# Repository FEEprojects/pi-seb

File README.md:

# Pi-Seb

A PCB for the Raspberry Pi to create a flexible sensor evaluation board.

Provides the following features:
* HAT identification EEPROM
* 12V DC input
* Battery backed RTC
* Temperature/Humidity Sensor
* 8 differential ADC
* 23 GPIO
* 8 I2C connectors
* 4 SPI connectors
* Debug LEDs (can be disabled)
* 4 port USB hub
  * RS232 connection / TTL Serial
  * 2 TTL Serial ports
  * RS485 connection
* Pycom Socket
  * SD card
  * Control of Raspberry Pi Power
  * 2 TTL Serial ports
  * I2C connection
  * SPI port
  * 8 GPIO

## Assembly
Most of the passives and some of the semi conductors are available in the Seeed studio OPL, additional components then need to be sourced and hand soldred.

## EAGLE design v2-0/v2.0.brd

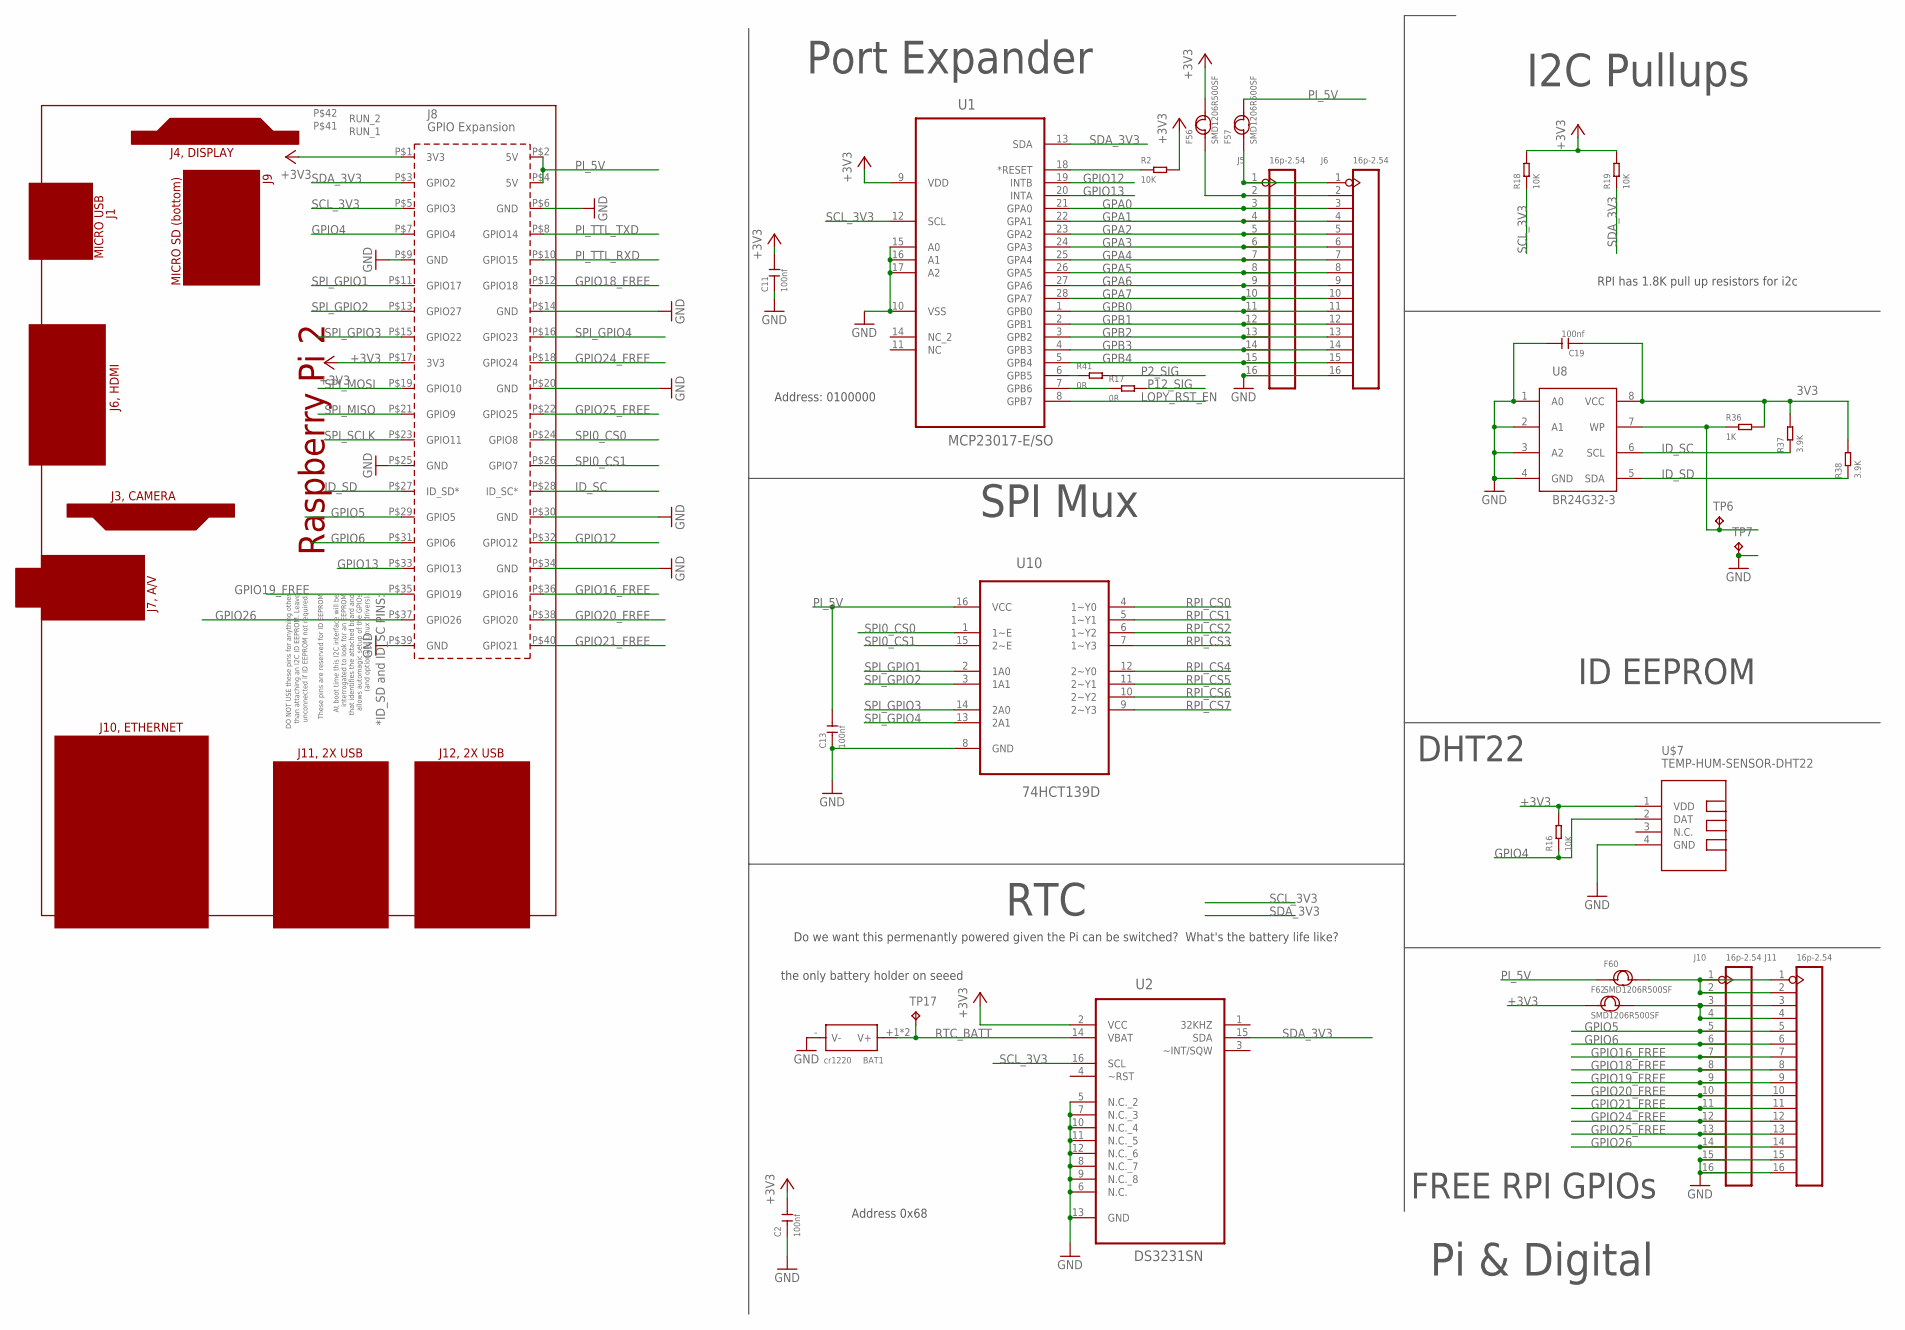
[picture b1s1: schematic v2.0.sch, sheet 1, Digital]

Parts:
BAT1: cr1220; BAT2P-13.5-CR1220
C2, C11, C13, C19: 100nf; C0603
F56, F57, F60, F62: SMD1206R500SF; F1206
J5, J6, J10, J11: 16p-2.54; H16-2.54
PCB1: RPI2
R2, R16, R18, R19: 10K; R0603
R17, R41: 0R; R0603
R36: 1K; R0603
R37, R38: 3.9K; R0603
TP6, TP7, TP17: TPB2,54; B2,54
U1: MCP23017-E/SO; SOIC127P1032X265-28N
U2: DS3231SN; SOIC127P1032X265-16N
U8: BR24G32-3; SOP8
U10: 74HCT139D; SOIC127P600X175-16N
U$7: TEMP-HUM-SENSOR-DHT22

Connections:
3V3: C19.1, R36.2, R37.2, R38.2, U8.8 (VCC)
+3V3: C2.2, C11.2, F56.2, F62.1, PCB1.P$1 (3V3), PCB1.P$17 (3V3), R2.2, R16.2, R18.2, R19.2, U1.9 (VDD), U2.2 (VCC), U$7.1 (VDD); also elsewhere on the board
EEPROM_WP: R36.1, TP6.TP, U8.7 (WP)
EXP_3V3: F56.1, J5.2, J6.2
EXP_5V: F57.1, J5.1, J6.1
GND: BAT1.- (V-), C2.1, C11.1, C13.1, C19.2, J5.16, J6.16, J10.15, J10.16, J11.15, J11.16, PCB1.P$6 (GND), PCB1.P$9 (GND), PCB1.P$14 (GND), PCB1.P$20 (GND), PCB1.P$25 (GND), PCB1.P$30 (GND), PCB1.P$34 (GND), PCB1.P$39 (GND), TP7.TP, U1.10 (VSS), U1.15 (A0), U1.16 (A1), U1.17 (A2), U2.5 (N.C._2), U2.6 (N.C.), U2.7 (N.C._3), U2.8 (N.C._7), U2.9 (N.C._8), U2.10 (N.C._4), U2.11 (N.C._5), U2.12 (N.C._6), U2.13 (GND), U8.1 (A0), U8.2 (A1), U8.3 (A2), U8.4 (GND), U10.8 (GND), U$7.4 (GND); also elsewhere on the board
GPA0: J5.3, J6.3, U1.21 (GPA0)
GPA1: J5.4, J6.4, U1.22 (GPA1)
GPA2: J5.5, J6.5, U1.23 (GPA2)
GPA3: J5.6, J6.6, U1.24 (GPA3)
GPA4: J5.7, J6.7, U1.25 (GPA4)
GPA5: J5.8, J6.8, U1.26 (GPA5)
GPA6: J5.9, J6.9, U1.27 (GPA6)
GPA7: J5.10, J6.10, U1.28 (GPA7)
GPB0: J5.11, J6.11, U1.1 (GPB0)
GPB1: J5.12, J6.12, U1.2 (GPB1)
GPB2: J5.13, J6.13, U1.3 (GPB2)
GPB3: J5.14, J6.14, U1.4 (GPB3)
GPB4: J5.15, J6.15, U1.5 (GPB4)
GPIO4: PCB1.P$7 (GPIO4), R16.1, U$7.2 (DAT)
GPIO5: J10.5, J11.5, PCB1.P$29 (GPIO5)
GPIO6: J10.6, J11.6, PCB1.P$31 (GPIO6)
GPIO12: PCB1.P$32 (GPIO12), U1.19 (INTB)
GPIO13: PCB1.P$33 (GPIO13), U1.20 (INTA)
GPIO16_FREE: J10.7, J11.7, PCB1.P$36 (GPIO16)
GPIO18_FREE: J10.8, J11.8, PCB1.P$12 (GPIO18)
GPIO19_FREE: J10.9, J11.9, PCB1.P$35 (GPIO19)
GPIO20_FREE: J10.10, J11.10, PCB1.P$38 (GPIO20)
GPIO21_FREE: J10.11, J11.11, PCB1.P$40 (GPIO21)
GPIO24_FREE: J10.12, J11.12, PCB1.P$18 (GPIO24)
GPIO25_FREE: J10.13, J11.13, PCB1.P$22 (GPIO25)
GPIO26: J10.14, J11.14, PCB1.P$37 (GPIO26)
GPIO_5V_FUSED: F60.2, J10.1, J10.2, J11.1, J11.2
ID_SC: PCB1.P$28 (ID_SC*), R37.1, U8.6 (SCL)
ID_SD: PCB1.P$27 (ID_SD*), R38.1, U8.5 (SDA)
LOPY_RST_EN: U1.8 (GPB7); also elsewhere on the board
unnamed: R2.1, U1.18 (*RESET)
unnamed: F62.2, J10.3, J10.4, J11.3, J11.4
P2_EN: R41.1, U1.6 (GPB5)
P2_SIG: R41.2; also elsewhere on the board
P12_SIG: R17.2; also elsewhere on the board
PI12_EN: R17.1, U1.7 (GPB6)
PI_5V: C13.2, F57.2, F60.1, PCB1.P$2 (5V), PCB1.P$4 (5V), U10.16 (VCC); also elsewhere on the board
PI_TTL_RXD: PCB1.P$10 (GPIO15); also elsewhere on the board
PI_TTL_TXD: PCB1.P$8 (GPIO14); also elsewhere on the board
RPI_CS0: U10.4 (1~Y0); also elsewhere on the board
RPI_CS1: U10.5 (1~Y1); also elsewhere on the board
RPI_CS2: U10.6 (1~Y2); also elsewhere on the board
RPI_CS3: U10.7 (1~Y3); also elsewhere on the board
RPI_CS4: U10.12 (2~Y0); also elsewhere on the board
RPI_CS5: U10.11 (2~Y1); also elsewhere on the board
RPI_CS6: U10.10 (2~Y2); also elsewhere on the board
RPI_CS7: U10.9 (2~Y3); also elsewhere on the board
RTC_BATT: BAT1.+1 (V+), BAT1.+2 (V+), TP17.TP, U2.14 (VBAT)
SCL_3V3: PCB1.P$5 (GPIO3), R18.1, U1.12 (SCL), U2.16 (SCL); also elsewhere on the board
SDA_3V3: PCB1.P$3 (GPIO2), R19.1, U1.13 (SDA), U2.15 (SDA); also elsewhere on the board
SPI0_CS0: PCB1.P$24 (GPIO8), U10.1 (1~E)
SPI0_CS1: PCB1.P$26 (GPIO7), U10.15 (2~E)
SPI_GPIO1: PCB1.P$11 (GPIO17), U10.2 (1A0)
SPI_GPIO2: PCB1.P$13 (GPIO27), U10.3 (1A1)
SPI_GPIO3: PCB1.P$15 (GPIO22), U10.14 (2A0)
SPI_GPIO4: PCB1.P$16 (GPIO23), U10.13 (2A1)
SPI_MISO: PCB1.P$21 (GPIO9); also elsewhere on the board
SPI_MOSI: PCB1.P$19 (GPIO10); also elsewhere on the board
SPI_SCLK: PCB1.P$23 (GPIO11); also elsewhere on the board

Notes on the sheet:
Pi & Digital
Port Expander
SPI Mux
RTC
I2C Pullups
Do we want this permenantly powered given the Pi can be switched? What's the battery life like?
RPI has 1.8K pull up resistors for i2c
the only battery holder on seeed
ID EEPROM
Address: 0100000
DHT22
FREE RPI GPIOs
Address 0x68

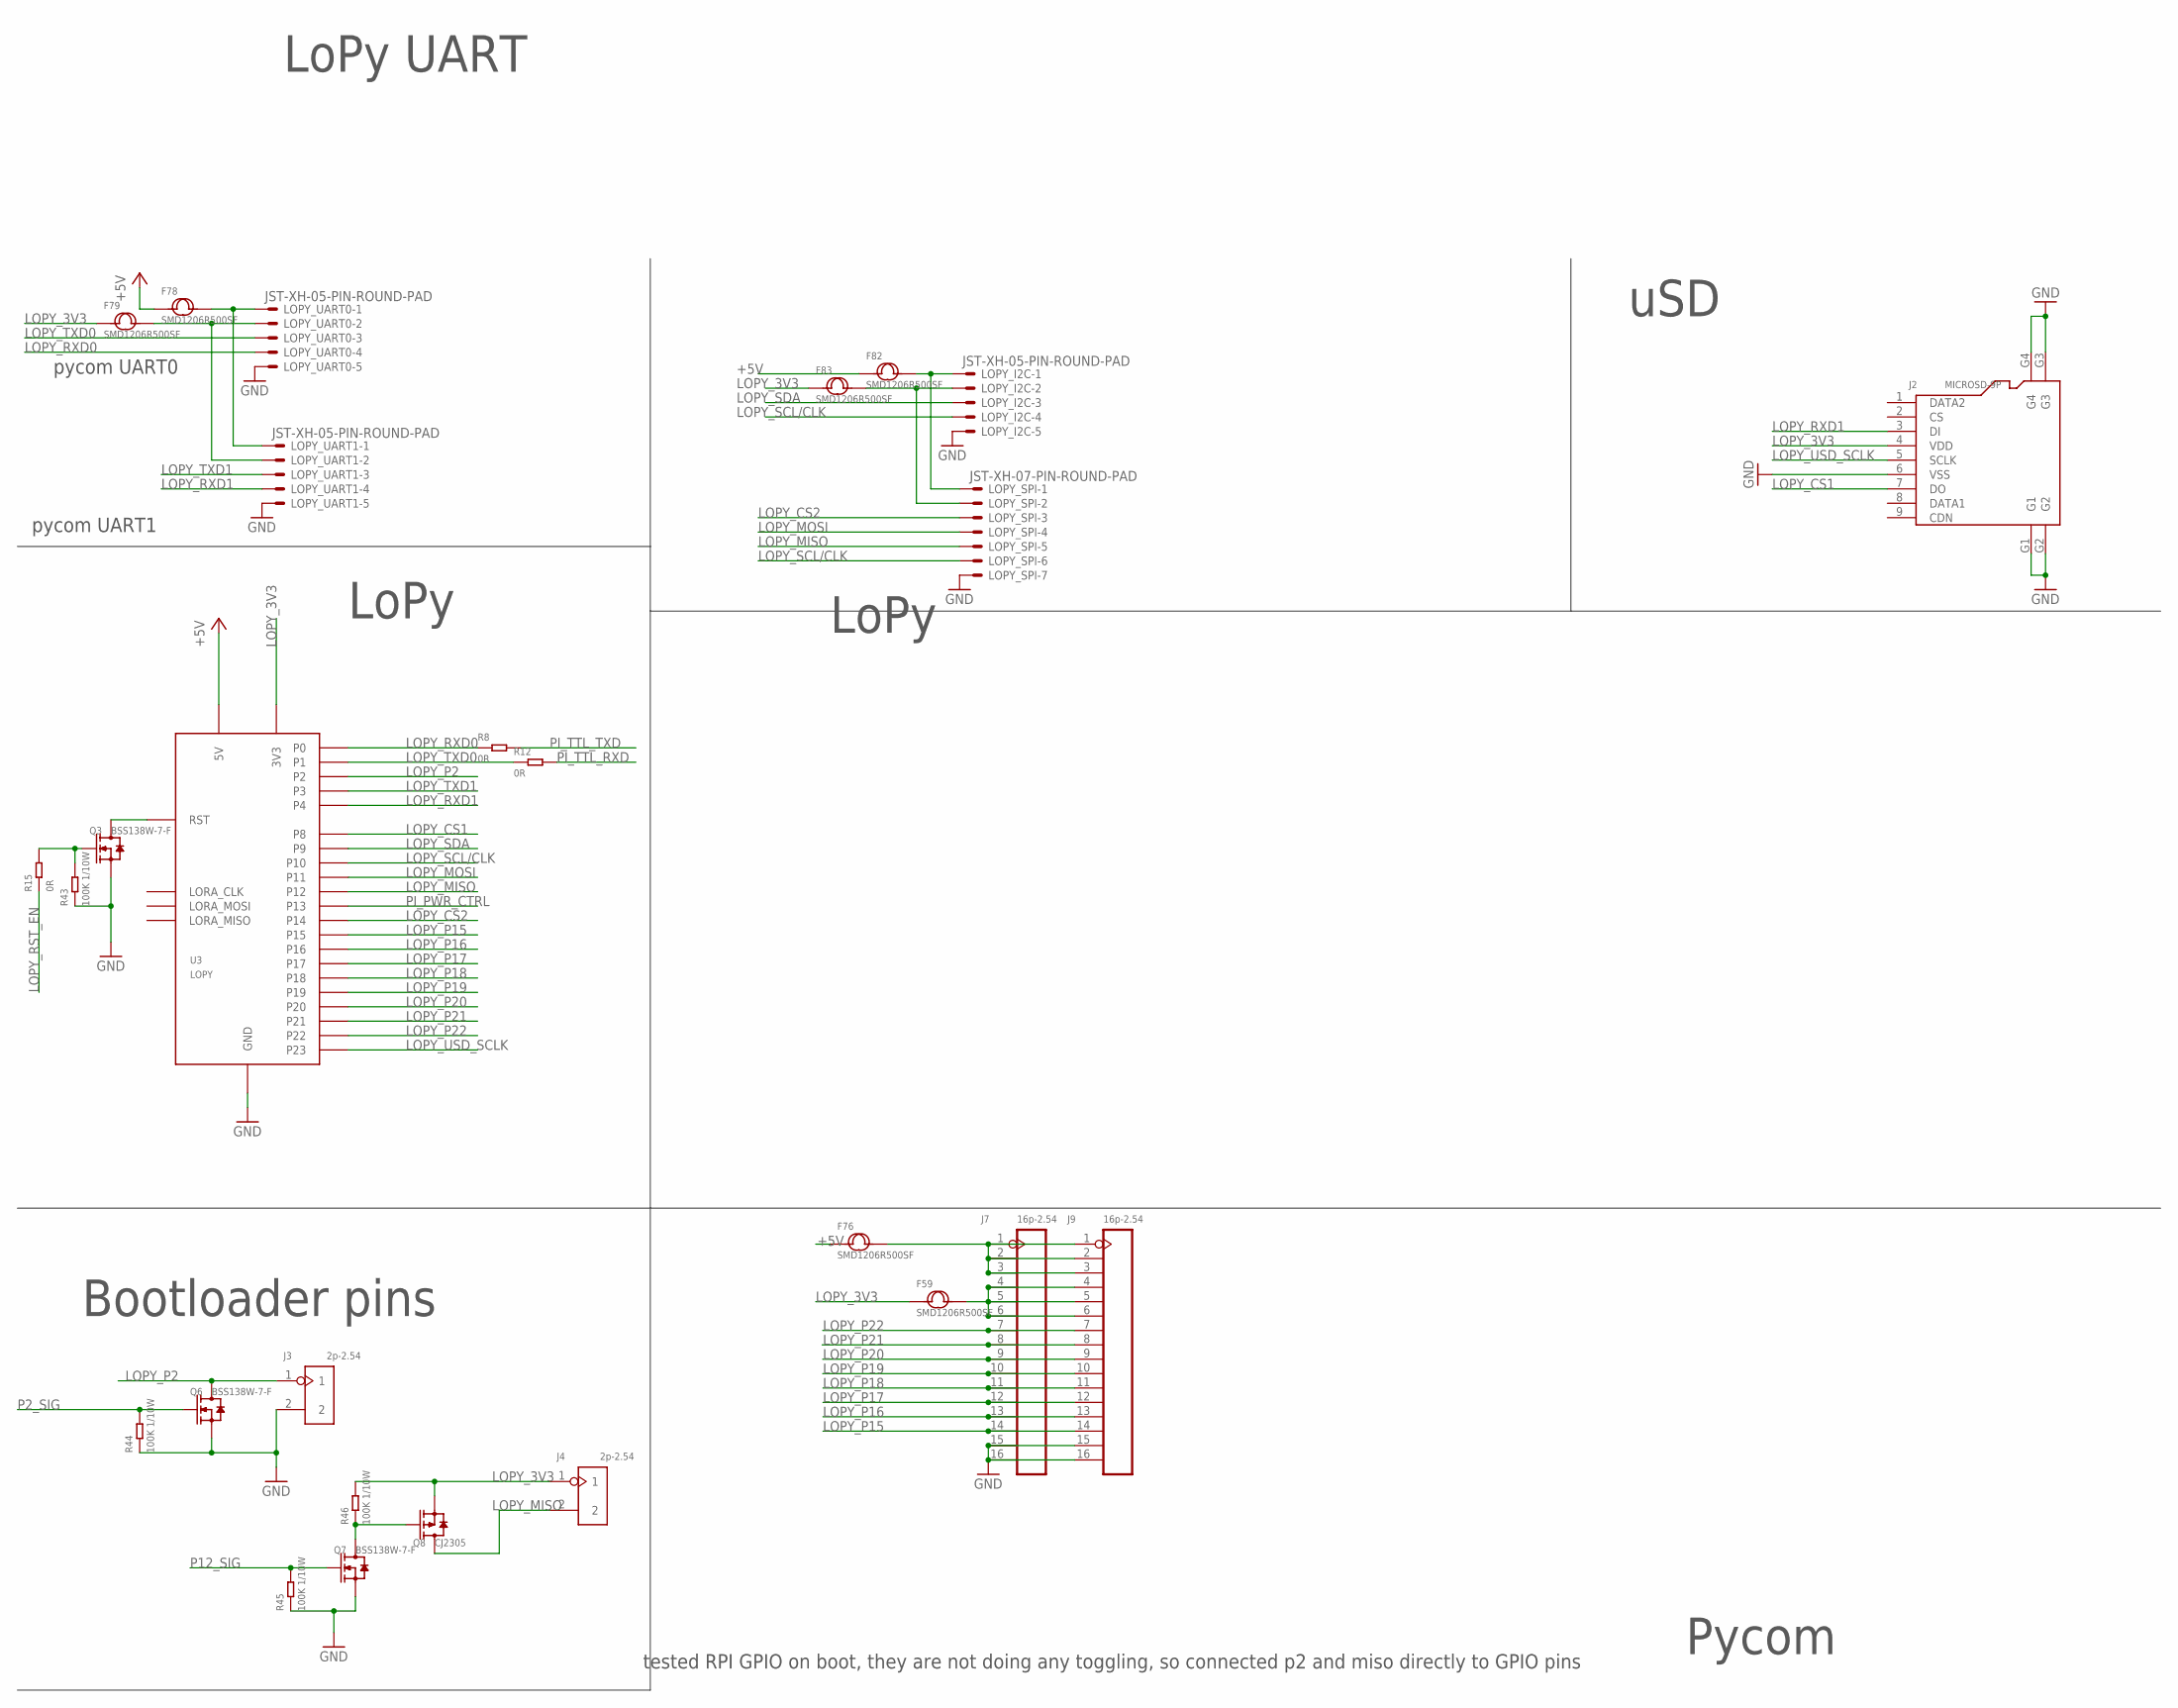
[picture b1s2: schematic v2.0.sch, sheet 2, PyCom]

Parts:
F59, F76, F78, F79, F82, F83: SMD1206R500SF; F1206
J2: MICROSD-9P; MICRO-SD9+4P-SMD-16.1X14.5X1.85MM
J3, J4: 2p-2.54; H2-2.54
J7, J9: 16p-2.54; H16-2.54
LOPY_I2C: JST-XH-05-PIN-ROUND-PAD; JST-XH-05-PACKAGE-ROUND-PAD
LOPY_SPI: JST-XH-07-PIN-ROUND-PAD; JST-XH-07-PACKAGE-ROUND-PAD
LOPY_UART0, LOPY_UART1: JST-XH-05-PIN-ROUND-PAD; JST-XH-05-PACKAGE-ROUND-PAD
Q3, Q6, Q7: BSS138W-7-F; SOT-23
Q8: CJ2305; SOT-23
R8, R12, R15: 0R; R0603
R43, R44, R45, R46: 100K 1/10W; R0603
U3: LOPY

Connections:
+5V: F76.1, F78.1, F82.1, U3.P$28 (5V); also elsewhere on the board
GND: J2.6 (VSS), J2.G1, J2.G2, J2.G3, J2.G4, J3.2, J7.15, J7.16, J9.15, J9.16, LOPY_I2C.5, LOPY_SPI.7, LOPY_UART0.5, LOPY_UART1.5, Q3.2 (S), Q6.2 (S), Q7.2 (S), R43.1, R44.1, R45.1, U3.P$27 (GND); also elsewhere on the board
LOPY_3V3: F59.1, F79.1, F83.1, J2.4 (VDD), J4.1, Q8.2 (S), R46.2, U3.P$26 (3V3); also elsewhere on the board
LOPY_3V3_FUSED: F59.2, J7.4, J7.5, J7.6, J9.4, J9.5, J9.6
LOPY_5V_FUSED: F76.2, J7.1, J7.2, J7.3, J9.1, J9.2, J9.3
LOPY_CS1: J2.7 (DO), U3.P$10 (P8)
LOPY_CS2: LOPY_SPI.3, U3.P$16 (P14)
LOPY_I2C_3V3_PROTECTED: F83.2, LOPY_I2C.2, LOPY_SPI.2
LOPY_MISO: J4.2, LOPY_SPI.5, Q8.3 (D), U3.P$14 (P12)
LOPY_MOSI: LOPY_SPI.4, U3.P$13 (P11)
LOPY_P2: J3.1, Q6.3 (D), U3.P$4 (P2)
LOPY_P15: J7.14, J9.14, U3.P$17 (P15)
LOPY_P16: J7.13, J9.13, U3.P$18 (P16)
LOPY_P17: J7.12, J9.12, U3.P$19 (P17)
LOPY_P18: J7.11, J9.11, U3.P$20 (P18)
LOPY_P19: J7.10, J9.10, U3.P$21 (P19)
LOPY_P20: J7.9, J9.9, U3.P$22 (P20)
LOPY_P21: J7.8, J9.8, U3.P$23 (P21)
LOPY_P22: J7.7, J9.7, U3.P$24 (P22)
LOPY_RST: Q3.3 (D), U3.P$1 (RST)
LOPY_RST_EN: R15.1; also elsewhere on the board
LOPY_RXD0: LOPY_UART0.4, R8.1, U3.P$2 (P0)
LOPY_RXD1: J2.3 (DI), LOPY_UART1.4, U3.P$6 (P4)
LOPY_SCL/CLK: LOPY_I2C.4, LOPY_SPI.6, U3.P$12 (P10)
LOPY_SDA: LOPY_I2C.3, U3.P$11 (P9)
LOPY_TXD0: LOPY_UART0.3, R12.1, U3.P$3 (P1)
LOPY_TXD1: LOPY_UART1.3, U3.P$5 (P3)
LOPY_UART0_3V3_PROTECTED: F79.2, LOPY_UART0.2, LOPY_UART1.2
LOPY_UART0_5V_PROTECTED: F78.2, LOPY_UART0.1, LOPY_UART1.1
LOPY_USD_SCLK: J2.5 (SCLK), U3.P$25 (P23)
unnamed: F82.2, LOPY_I2C.1, LOPY_SPI.1
unnamed: Q3.1 (G), R15.2, R43.2
unnamed: Q7.3 (D), Q8.1 (G), R46.1
P2_SIG: Q6.1 (G), R44.2; also elsewhere on the board
P12_SIG: Q7.1 (G), R45.2; also elsewhere on the board
PI_PWR_CTRL: U3.P$15 (P13); also elsewhere on the board
PI_TTL_RXD: R12.2; also elsewhere on the board
PI_TTL_TXD: R8.2; also elsewhere on the board

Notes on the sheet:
Pycom
pycom UART1
pycom UART0
LoPy
LoPy UART
uSD
tested RPI GPIO on boot, they are not doing any toggling, so connected p2 and miso directly to GPIO pins
Bootloader pins

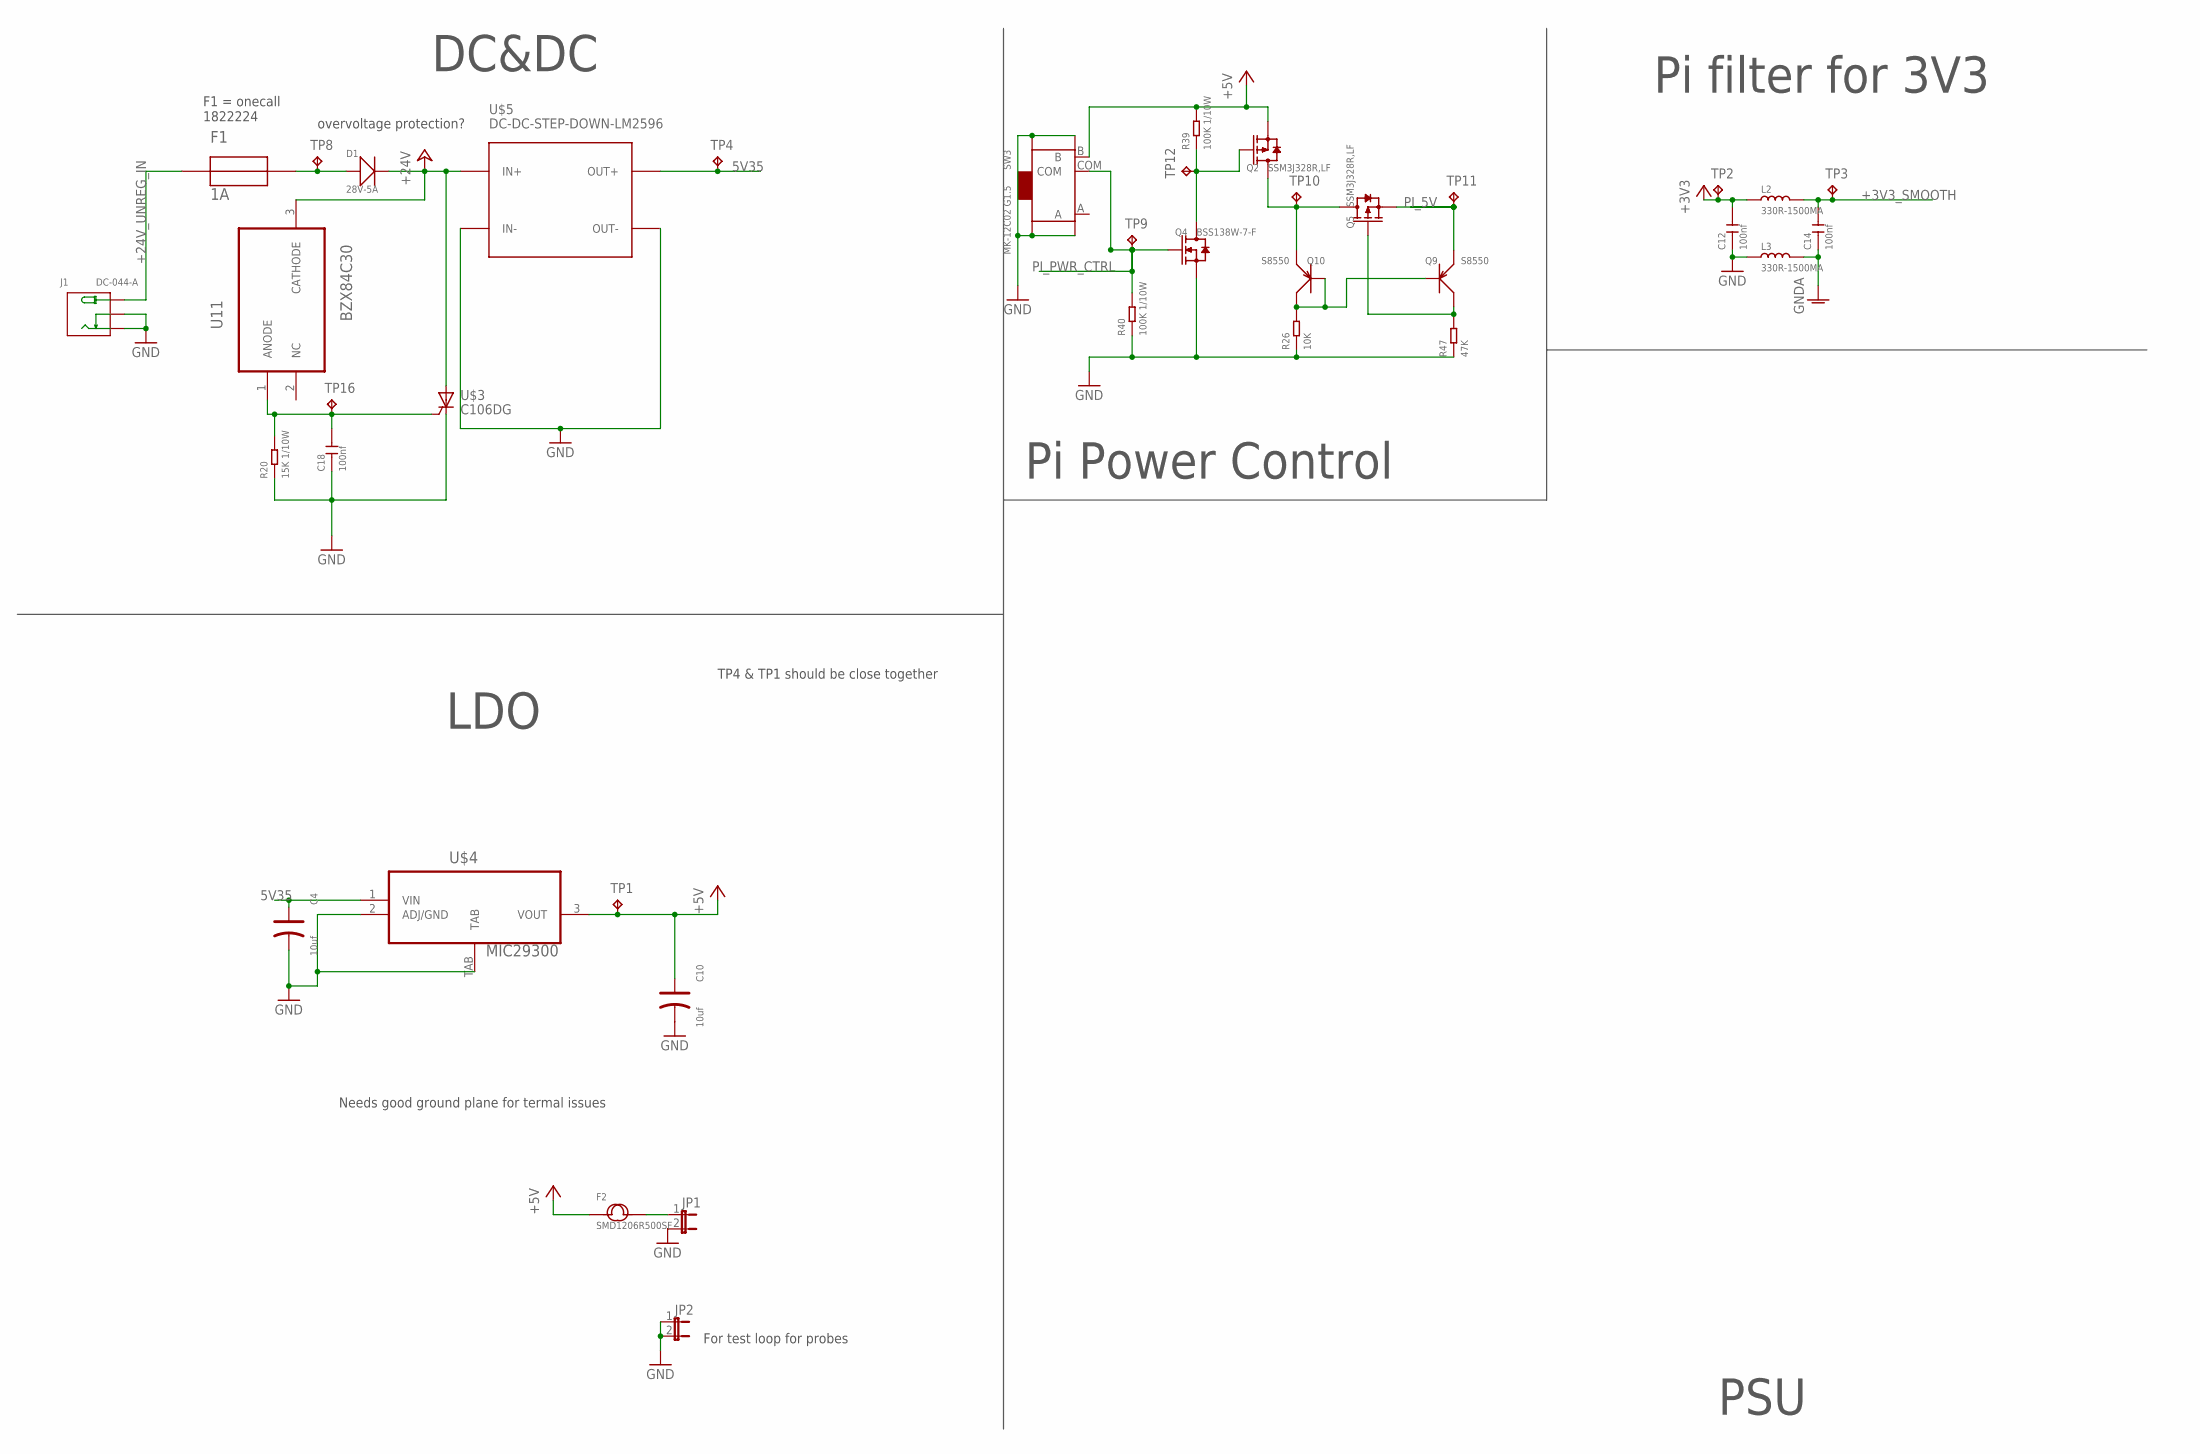
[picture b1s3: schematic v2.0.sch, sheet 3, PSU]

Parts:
C4, C10: 10uf; AVX-A
C12, C14, C18: 100nf; C0603
D1: 28V-5A; DO-214AA
F1: 1A; 2920
F2: SMD1206R500SF; F1206
J1: DC-044-A; DCJ3P-11.6X9.6X7.0MM
JP1, JP2: JP1E; JP1
L2, L3: 330R-1500MA; L0805
Q2, Q5: SSM3J328R,LF; SOT-23
Q4: BSS138W-7-F; SOT-23
Q9, Q10: S8550; SOT-23
R20: 15K 1/10W; R0603
R26: 10K; R0603
R39, R40: 100K 1/10W; R0603
R47: 47K; R0603
SW3: MK-12C02 G1.5; SW7-SMD-L6.7X2.7X3.2MM
TP1, TP2, TP3, TP4, TP8, TP9, TP10, TP11, TP12, TP16: TPB2,54; B2,54
U11: BZX84C30; SOT91P240X110-3N
U$3: C106DG; TO-225AA
U$4: MIC29300; TO-263
U$5: DC-DC-STEP-DOWN-LM2596

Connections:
5V35: C4.+, TP4.TP, U$4.1 (VIN), U$5.OUT+; also elsewhere on the board
+3V3: C12.2, L2.1, TP2.TP; also elsewhere on the board
+3V3_SMOOTH: C14.2, L2.2, TP3.TP; also elsewhere on the board
+5V: C10.+, F2.1, Q2.2 (S), R39.2, SW3.B, TP1.TP, U$4.3 (VOUT); also elsewhere on the board
+24V: D1.-, U11.3 (CATHODE), U$3.2 (A), U$5.IN+; also elsewhere on the board
+24V_UNREG_IN: F1.1, J1.+
GND: C4.-, C10.-, C12.1, C18.1, J1.-, J1.CDN, JP1.2, JP2.1, JP2.2, L3.1, Q4.2 (S), R20.1, R26.1, R40.1, R47.1, SW3.SS1, SW3.SS2, SW3.SS3, SW3.SS4, U$3.1 (C), U$4.2 (ADJ/GND), U$4.TAB, U$5.IN-, U$5.OUT-; also elsewhere on the board
GNDA: C14.1, L3.2; also elsewhere on the board
unnamed: F2.2, JP1.1
unnamed: Q9.1 (B), Q10.1 (B), Q10.3 (C), R26.2
unnamed: Q5.1 (G), Q9.3 (C), R47.2
unnamed: D1.+, F1.2, TP8.TP
unnamed: C18.2, R20.2, TP16.TP, U11.1 (ANODE), U$3.3 (G1)
unnamed: Q2.3 (D), Q5.3 (D), Q10.2 (E), TP10.TP
unnamed: Q2.1 (G), Q4.3 (D), R39.1, TP12.TP
PI_5V: Q5.2 (S), Q9.2 (E), TP11.TP; also elsewhere on the board
PI_PWR_CTRL: Q4.1 (G), R40.2, SW3.COM, TP9.TP; also elsewhere on the board

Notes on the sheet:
PSU
LDO
DC&DC
Pi filter for 3V3
overvoltage protection?
Pi Power Control
Needs good ground plane for termal issues
TP4 & TP1 should be close together
F1 = onecall 1822224
For test loop for probes

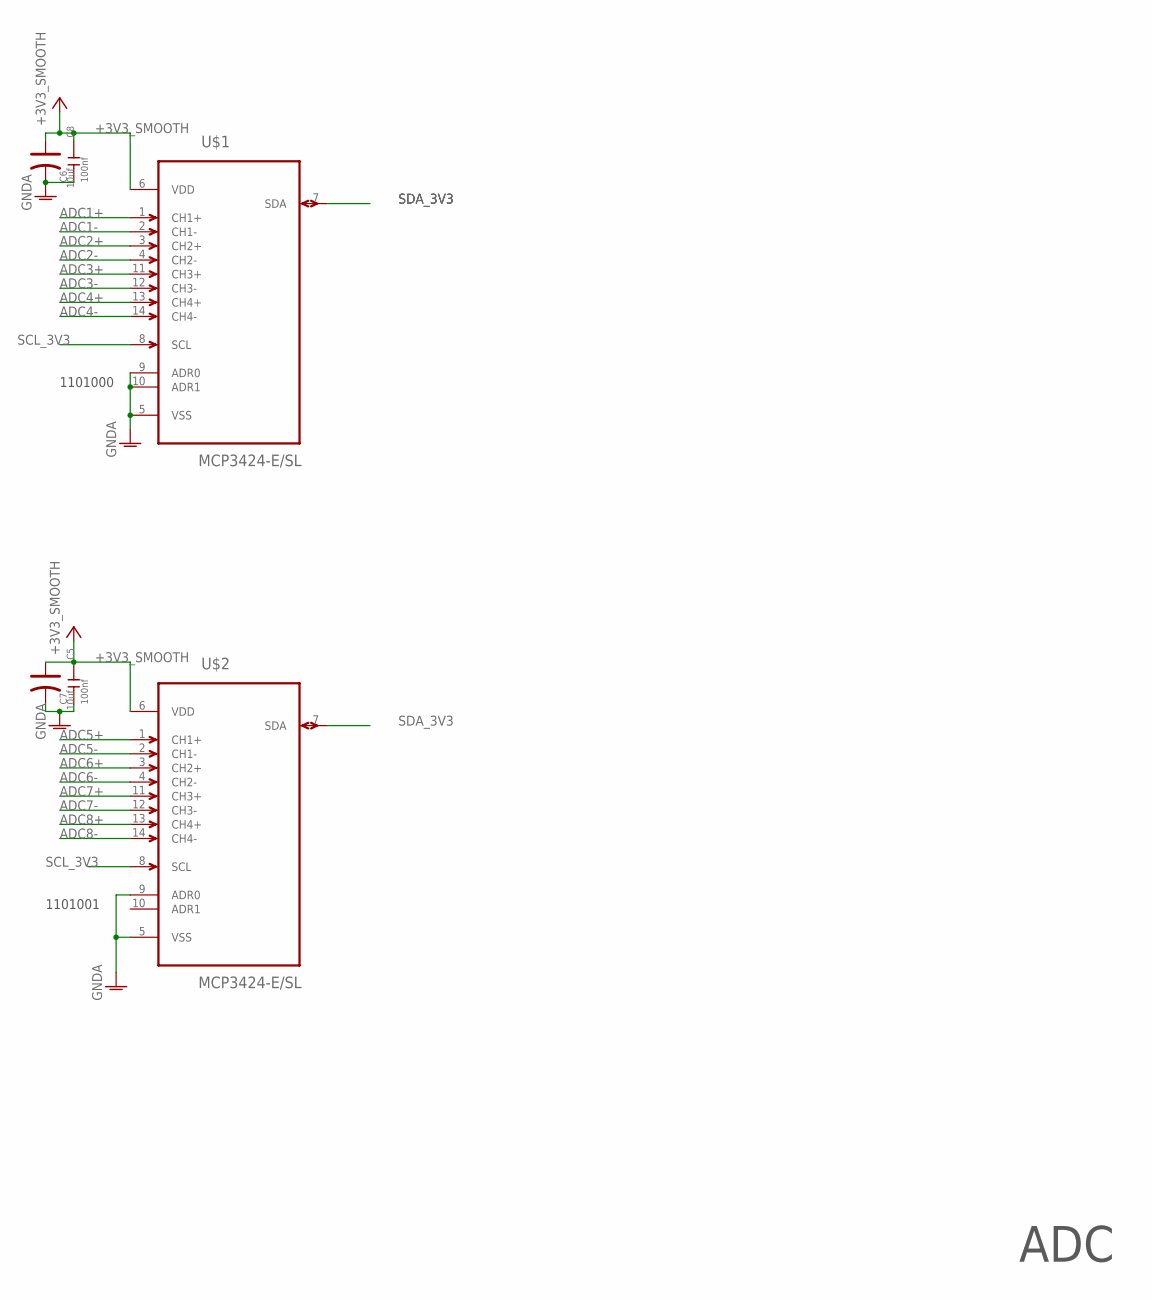
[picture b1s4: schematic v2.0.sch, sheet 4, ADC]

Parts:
C5, C8: 10uf; AVX-A
C6, C7: 100nf; C0603
U$1, U$2: MCP3424-E/SL; SOIC127P600X175-14N

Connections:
+3V3_SMOOTH: C5.+, C6.2, C7.2, C8.+, U$1.6 (VDD), U$2.6 (VDD); also elsewhere on the board
ADC1+: U$1.1 (CH1+); also elsewhere on the board
ADC1-: U$1.2 (CH1-); also elsewhere on the board
ADC2+: U$1.3 (CH2+); also elsewhere on the board
ADC2-: U$1.4 (CH2-); also elsewhere on the board
ADC3+: U$1.11 (CH3+); also elsewhere on the board
ADC3-: U$1.12 (CH3-); also elsewhere on the board
ADC4+: U$1.13 (CH4+); also elsewhere on the board
ADC4-: U$1.14 (CH4-); also elsewhere on the board
ADC5+: U$2.1 (CH1+); also elsewhere on the board
ADC5-: U$2.2 (CH1-); also elsewhere on the board
ADC6+: U$2.3 (CH2+); also elsewhere on the board
ADC6-: U$2.4 (CH2-); also elsewhere on the board
ADC7+: U$2.11 (CH3+); also elsewhere on the board
ADC7-: U$2.12 (CH3-); also elsewhere on the board
ADC8+: U$2.13 (CH4+); also elsewhere on the board
ADC8-: U$2.14 (CH4-); also elsewhere on the board
GNDA: C5.-, C6.1, C7.1, C8.-, U$1.5 (VSS), U$1.9 (ADR0), U$1.10 (ADR1), U$2.5 (VSS), U$2.9 (ADR0); also elsewhere on the board
SCL_3V3: U$1.8 (SCL), U$2.8 (SCL); also elsewhere on the board
SDA_3V3: U$1.7 (SDA), U$2.7 (SDA); also elsewhere on the board

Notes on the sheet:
ADC
1101000
1101001

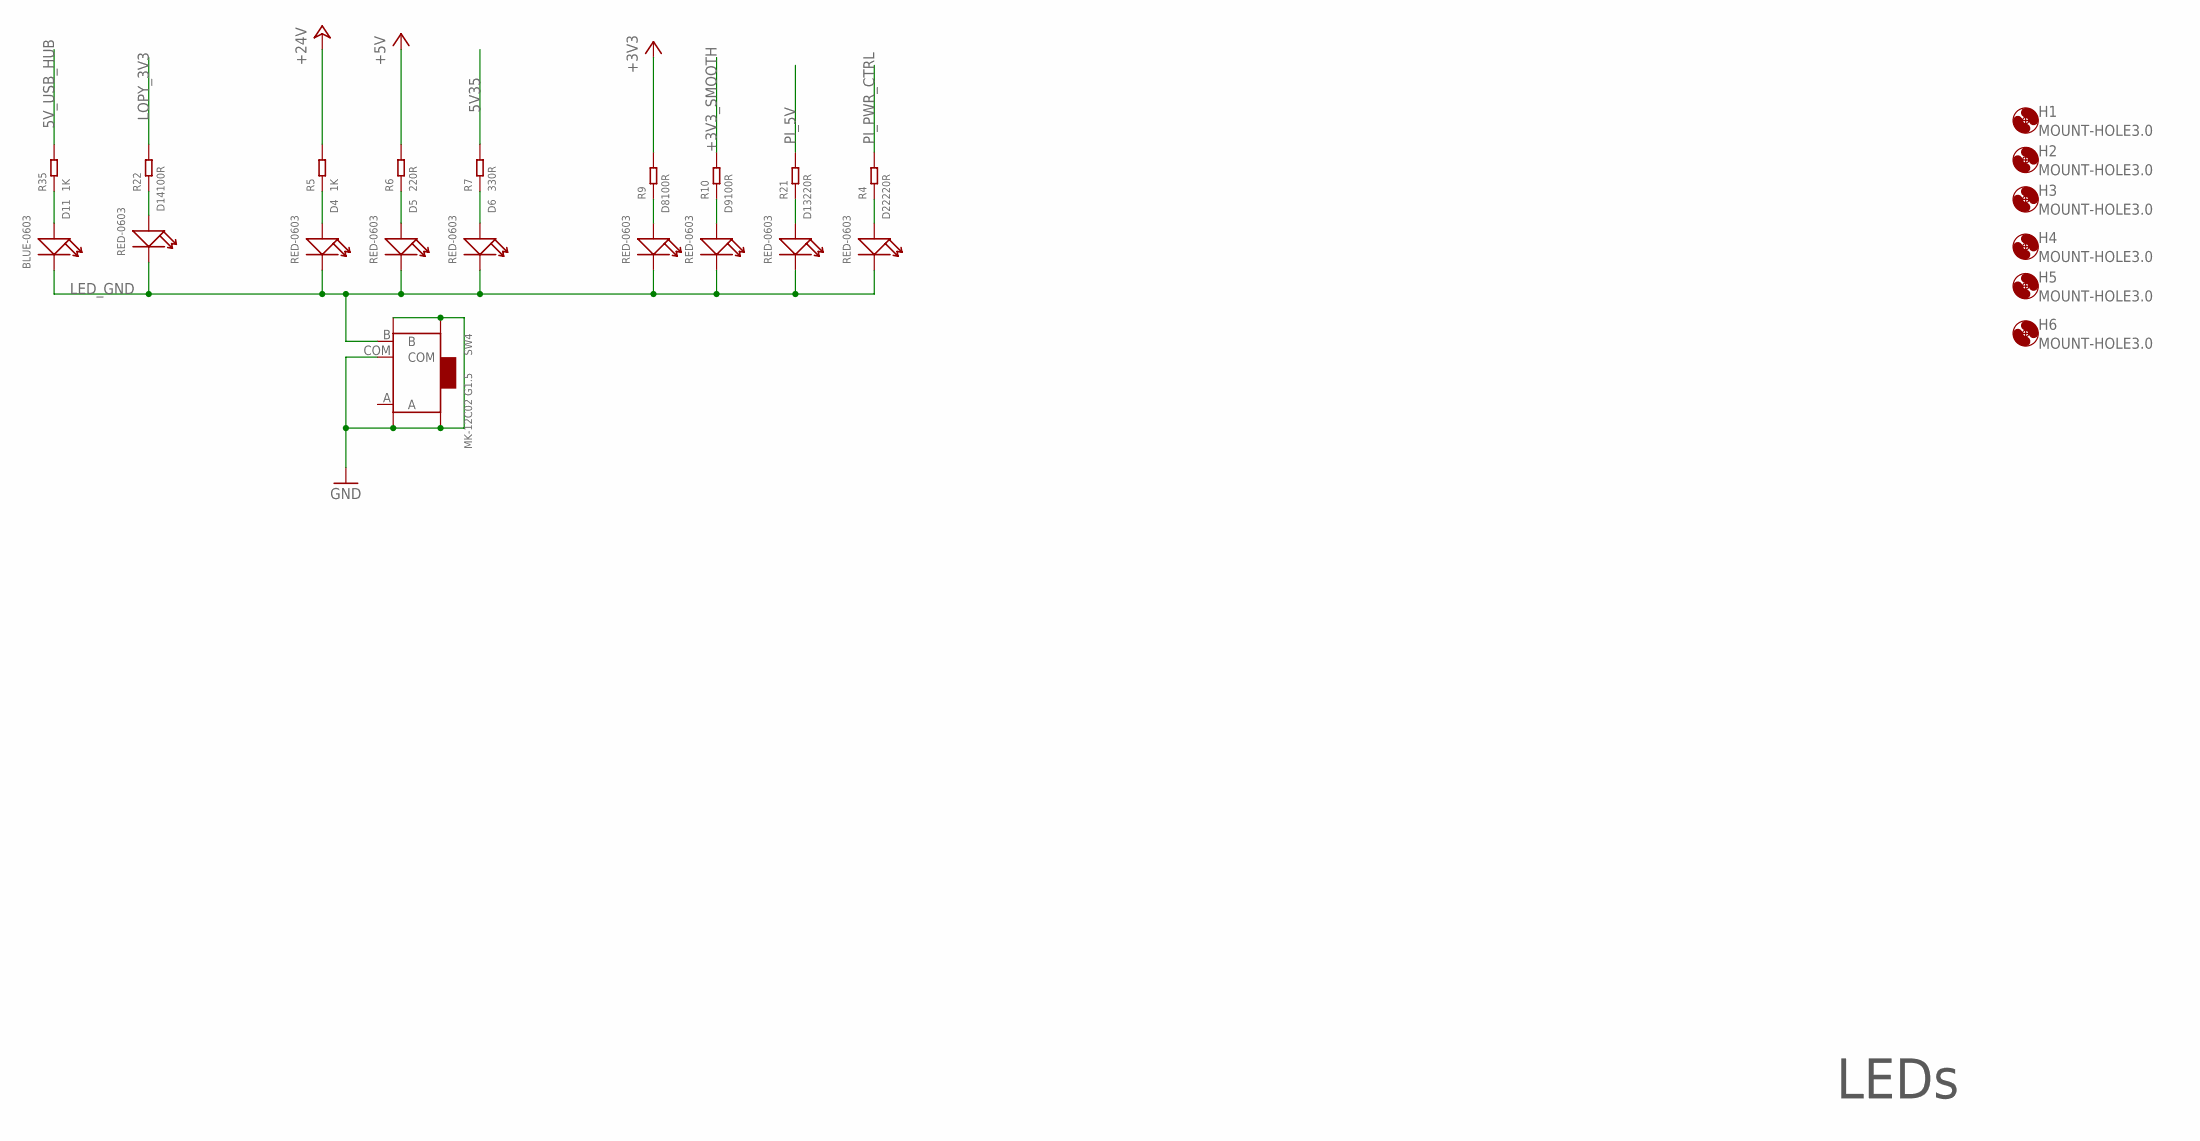
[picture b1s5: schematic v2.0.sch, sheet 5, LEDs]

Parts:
D4, D5, D6, D8, D9, D13, D14, D22: RED-0603; LED-0603
D11: BLUE-0603; LED-0603
H1, H2, H3, H4, H5, H6: MOUNT-HOLE3.0; 3,0
R4, R6, R21: 220R; R0603
R5, R35: 1K; R0603
R7: 330R; R0603
R9, R10, R22: 100R; R0603
SW4: MK-12C02 G1.5; SW7-SMD-L6.7X2.7X3.2MM

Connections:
5V35: R7.2; also elsewhere on the board
5V_USB_HUB: R35.2; also elsewhere on the board
+3V3: R9.2; also elsewhere on the board
+3V3_SMOOTH: R10.2; also elsewhere on the board
+5V: R6.2; also elsewhere on the board
+24V: R5.2; also elsewhere on the board
GND: SW4.COM, SW4.SS1, SW4.SS2, SW4.SS3, SW4.SS4; also elsewhere on the board
LED_GND: D4.-, D5.-, D6.-, D8.-, D9.-, D11.-, D13.-, D14.-, D22.-, SW4.B; also elsewhere on the board
LOPY_3V3: R22.2; also elsewhere on the board
unnamed: D22.+, R4.1
unnamed: D9.+, R10.1
unnamed: D8.+, R9.1
unnamed: D6.+, R7.1
unnamed: D5.+, R6.1
unnamed: D4.+, R5.1
unnamed: D11.+, R35.1
unnamed: D14.+, R22.1
unnamed: D13.+, R21.1
PI_5V: R21.2; also elsewhere on the board
PI_PWR_CTRL: R4.2; also elsewhere on the board

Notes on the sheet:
LEDs

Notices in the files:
parts and their libraries:
diy-modules: Released under the Creative Commons Attribution 4.0 International License: http://creativecommons.org/licenses/by/4.0
